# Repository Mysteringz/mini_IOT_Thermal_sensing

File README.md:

# CrowdAware

CrowdAware is a privacy-aware crowd monitoring prototype that uses low-resolution thermal sensors (MLX90640, 32x24) and edge processing on ESP32 nodes.

Instead of using RGB video, each node detects moving heat blobs, estimates person centroids, and transmits compact telemetry to a central receiver for live visualization and analytics.

## Why this project

Conventional crowd monitoring systems often trade privacy for visibility. CrowdAware is designed to keep personally identifying information out of the data path while still enabling:

- occupancy awareness
- movement and flow analysis
- congestion monitoring

## Current implementation status

This repository currently includes:

- ESP32 (Heltec WiFi LoRa 32 v3) node firmware for MLX90640 capture and on-device detection
- Wi-Fi UDP telemetry transport (current active path)
- Windows Python parser/visualizer for receiving and rendering node output
- hardware design files for a custom node PCB

The report references LoRaWAN architecture goals. In this codebase, Wi-Fi UDP is the active telemetry path used for development and visualization.

## Repository structure

```
Firmware/
	node/                          # ESP32 + MLX90640 node firmware
Visualization/
	parser_win.py                  # UDP receiver + OpenCV live visualizer
PCB Files/
	Altium Files/                  # Schematic + PCB source
	Gerber Files/                  # Manufacturing outputs
README.md
```

## System architecture

1. Sensor capture
- ESP32 reads thermal frames from MLX90640 (32x24) over I2C.

2. On-node processing
- Convert raw temperatures to 8-bit grayscale.
- Build/update a running background model.
- Detect moving hot regions with a lightweight pipeline.
- Extract person candidates (centroid and area).

3. Telemetry
- Serialize processing outputs and detections into a binary packet.
- Fragment into 4 UDP datagrams with sequence metadata.
- Transmit to the visualization host.

4. Central parsing and visualization
- Reassemble fragments.
- Decode intermediate images and detections.
- Render a 2x2 diagnostic view with overlays.

## Detection pipeline (firmware)

Implemented in the thermal processor:

1. Background subtraction
- Current frame minus running average background.

2. Morphological opening
- 3x3 erosion then 3x3 dilation to reduce noise and split weak bridges.

3. Gaussian blur
- 3x3 blur to smooth local artifacts.

4. Distance transform
- Approximate foreground distance map.

5. Watershed-like region extraction
- Connected-region labeling on thresholded distance map.
- Per-region centroid and area extraction.
- Area filtering via configurable min/max thresholds.

Adaptive behavior:

- Background is initialized over N frames.
- Background updates continue only when no people are detected to reduce contamination.

## Packet protocol

### Binary packet (reassembled payload)

- Header magic: `FE 01 FE 01`
- Payload length: uint16 little-endian
- Payload layout:
	- thermal image (768 bytes)
	- background image (768 bytes)
	- distance map (768 bytes)
	- labeled image (768 bytes)
	- num_detected (1 byte)
	- per detection: `y (1), x (1), area (uint16 LE)`

### UDP fragment packet

- Header magic: `FE 02 FE 02`
- Sequence: uint16 little-endian
- Fragment index: uint8
- Fragment count: uint8 (fixed at 4)
- Payload size: uint16 little-endian
- Payload bytes

Parser behavior:

- Waits for all 4 fragments for a `(sender_ip, sequence)` frame.
- Concatenates fragments in index order.
- Drops stale partial frames after timeout.

## Quick start

### 1) Firmware (Heltec WiFi LoRa 32 v3 node)

Prerequisites:

- Arduino IDE with Heltec WiFi LoRa 32(v3) board support
- MLX90640-compatible libraries required by the firmware

Open and configure:

- Sketch: `Firmware/node/node.ino`
- Main config: `Firmware/node/config.h`

Update at minimum:

- `WIFI_SSID`
- `WIFI_PASSWORD`
- `WIFI_REMOTE_IP_A..D` (host running parser)
- `WIFI_REMOTE_PORT` (default `5100`)
- `NODE_DEVICE_ID` (if using multiple nodes)

Upload firmware to ESP32, then open serial monitor (57600 baud) if needed for diagnostics.

### 2) Visualization receiver (Windows)

From repository root:

```powershell
pip install numpy opencv-python
python Visualization/parser_win.py
```

Expected behavior:

- Listener starts on `0.0.0.0:5100`.
- OpenCV window shows a 2x2 panel:
	- Raw image
	- Background
	- Distance map
	- Watershed labels
- Detected blobs and `(x,y)` coordinates are overlaid on the raw panel.

Press `q` to close the visualizer.

## Runtime tuning via serial commands

The firmware accepts newline-terminated commands over serial to tune processing without recompiling.

Supported command format:

```text
SET_DT_BG_THRESHOLD=<int>
SET_DT_MAX_DISTANCE=<int>
SET_MIN_PERSON_AREA=<int>
SET_MAX_PERSON_AREA=<int>
SET_BG_FRAME_COUNT=<int>
SET_TEMP_MIN=<float>
SET_TEMP_MAX=<float>
```

Notes:

- Changing `SET_BG_FRAME_COUNT` triggers background re-initialization.
- `TEMP_RANGE` is derived internally from min/max values.

## Hardware

Node hardware files are provided in:

- `PCB Files/Altium Files/`
- `PCB Files/Gerber Files/`

These include board-level design artifacts for the thermal node platform.

## Known limitations

- Current telemetry path in code is Wi-Fi UDP, not production LoRaWAN.
- Deployment and parameter management still rely on source-level/serial workflows.
- Multi-node global fusion and de-duplication are currently outside this repository's Python visualizer scope.

## Suggested next milestones

- Add a central server service for multi-node ingestion and global coordinate fusion.
- Build an operator/admin UI for node registration, calibration, and parameter control.
- Add replay logging and offline evaluation tools for algorithm benchmarking.

## Team

Innovation Wing IoT Team

- Ilo Japar
- Zhifang Li
- Nuth Kitchongcharoenying
- Netitorn Kawmali
- Pitimontreekul Chalida

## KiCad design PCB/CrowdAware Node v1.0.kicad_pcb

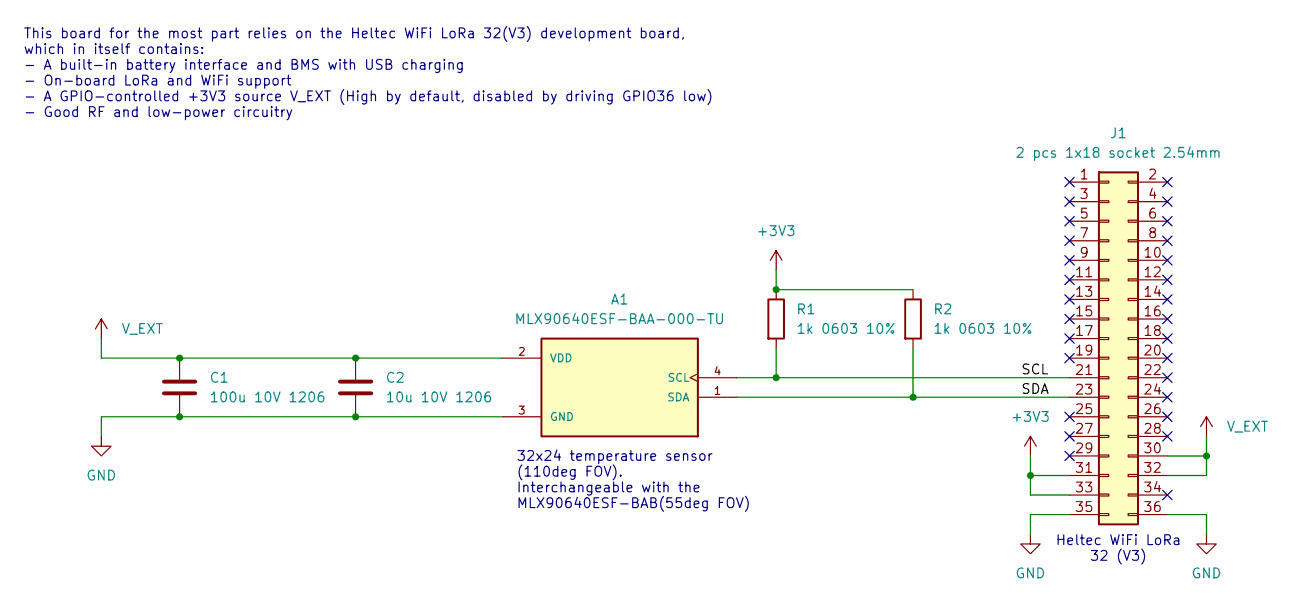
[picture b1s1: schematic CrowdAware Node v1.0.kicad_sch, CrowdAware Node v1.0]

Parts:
A1: MLX90640ESF-BAA-000-TU; PARTREV 11; Mouser No. 482-MLX90640ESFBAASP
C1: 100u 10V 1206; C_1206_3216Metric_Pad1.33x1.80mm_HandSolder; Mouser No. 81-GRM31CR61A107MA8L
C2: 10u 10V 1206; C_1206_3216Metric_Pad1.33x1.80mm_HandSolder; Mouser No. 81-GRM319R61A106KE9J
J1: 2 pcs 1x18 socket 2.54mm; Connector_HeltecWiFiLoRa32v3; Mouser No. 571-6-535541-6
R1, R2: 1k 0603 10%; R_0603_1608Metric_Pad0.98x0.95mm_HandSolder; Mouser No. 603-SR0603JR-7T1KL

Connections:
+3V3: J1.31, J1.33, R1.1, R2.1
/SCL: A1.4 (SCL), J1.21, R1.2
/SDA: A1.1 (SDA), J1.23, R2.2
GND: A1.3 (GND), C1.2, C2.2, J1.35, J1.36
V_EXT: A1.2 (VDD), C1.1, C2.1, J1.30, J1.32

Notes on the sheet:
This board for the most part relies on the Heltec WiFi LoRa 32(V3) development board, which in itself contains: - A built-in battery interface and BMS with USB charging - On-board LoRa and WiFi support - A GPIO-controlled +3V3 source V_EXT (High by default, disabled by driving GPIO36 low) - Good RF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
Heltec WiFi LoRa 32 (V3)
32x24 temperature sensor (110deg FOV). Interchangeable with the MLX90640ESF-BAB(55deg FOV)

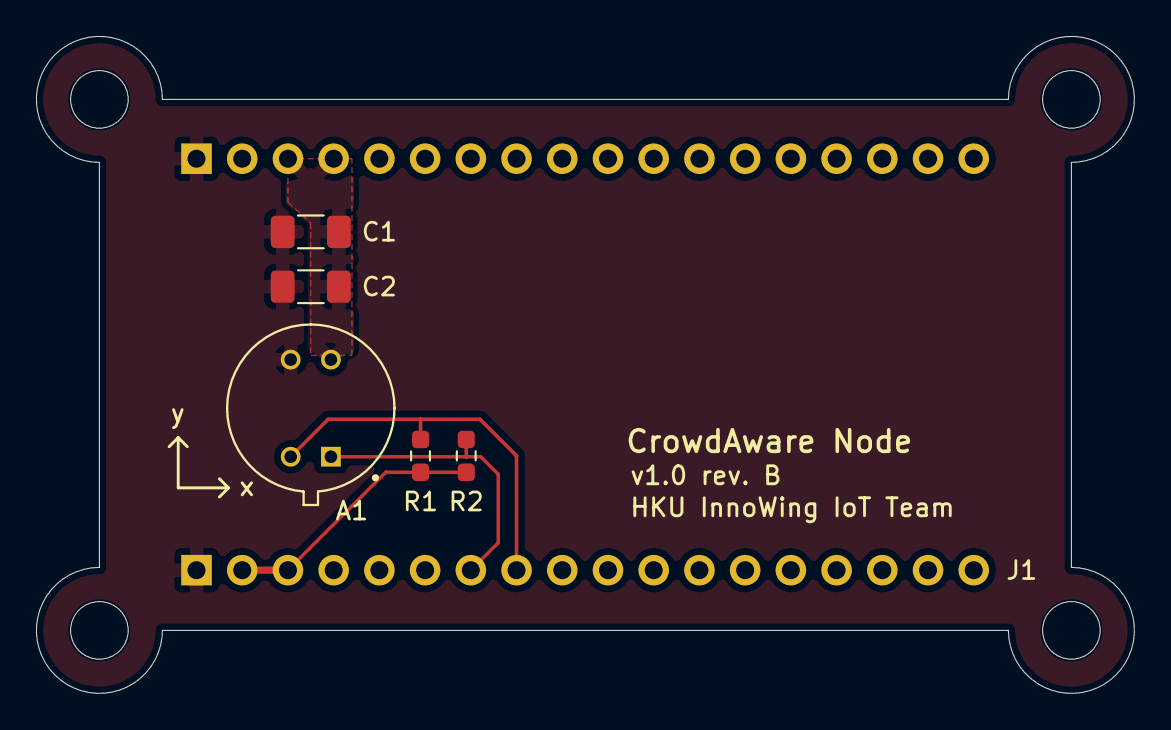
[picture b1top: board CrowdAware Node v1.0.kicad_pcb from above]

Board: 2 copper layers, 61.0 x 36.5 mm, 6 parts (1 on the bottom side), 5 nets.

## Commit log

2025-04-29 Rename plain_thermal_node.cpp to plain_thermal_node.ino
2025-06-03 Add visualization and cnn files and restructure repository
2025-06-11 Create PCB
2025-06-11 Create placeholder
2025-06-11 SCH Document
2025-06-11 Files for Altium (Schematics)
2025-06-19 Create Blank
2025-06-19 Create Spacer
2025-06-19 Version 1 of Thermal Camera PCB
2025-06-19 Delete Hardware/PCB directory
    Migrated over to home folder
2025-06-19 Delete PCB/Blank
    Cleanup
2025-06-19 Delete PCB/ThermalCamV1/Spacer
    Cleanup
2025-06-26 Added README file
2025-07-07 Delete PCB/ThermalCamV1 directory
    Updating to V1.2
2025-07-07 Spacer for PCB dir
2025-07-07 Updated to V1.1
2025-07-22 Uploaded PyTorch ONNX converter
2025-07-24 not working software, please fix
2025-07-24 Added feature testing for hardware and new lora+wifi code
2025-07-30 deleted broken files. Updated new version of normal thermal node with rgb based on people detection.
2025-08-01 Fixed num of LEDs. Change the indicator color to green.
2025-08-01 fix readme
2025-10-03 Update Readme with usage and requirements
    Added usage information about Arduino serial monitor and image processing requirements.
2025-10-03 Add STM32 code, model conversion pipeline, and ultralytics development
2025-10-03 Add TinyEngine Repository
2025-11-04 Add Mini TV Workshop Initial Code
2025-11-04 Move workshop folder location
2026-03-02 Removed Mini TV Repo from here; All relevant files already migrated to new Repo
2026-03-02 Added PCB Folder
2026-03-02 Moving files around in Hardware folder
2026-03-02 Reordered some functions
2026-03-04 Updated README.md due to deprecated Heltec board, structured into src files for Arduino, refactored out Web_interface
2026-03-04 Added incomplete README.md to thermal node 2.4, refactored camera_algorithm and web_interface
2026-03-05 Fixed type mismatch in OnDataSent; fixed type conflicts in refactored files
2026-03-05 Decided there was no point in putting everythin in subdirectories since Arduino is messy
2026-03-05 Fixed existing problems in Camera_algorithm, abstracted away struct_message into its own file (Data_packet), beginning refactoring for LED_Controller
2026-03-05 Fixed stray setup, now compiles properly
2026-03-06 Fixed led_set double declaration, factored out LoRaWAN server code to Web_interface, moved wifi, host, and ssid into user config
2026-03-06 Defined macros for LED Control
2026-03-11 Set correct lora params, fixed incorrect sequence flow, added serial print messages for more granular debugging
2026-03-30 Configured LoRa params as macros, added macros for led colours
2026-03-30 chore(repo): remove vendored YOLOv5 and third-party project
    Delete previously committed full source copies of YOLOv5 and another external OSS project.
    This cleans the repo and sets up a dependency-based install flow to be documented in the upcoming refactor README.
2026-03-30 Add thermal image processing and communication modules
    - Implemented serial communication for configurable parameters in `serial_comms.cpp` and `serial_comms.h`.
    - Developed thermal image processing algorithms in `thermal_image_processor.cpp` and `thermal_image_processor.h`, including background subtraction, morphological operations, and watershed segmentatio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
    - Created serialization functions for thermal data in `thermal_serializer.cpp` and `thermal_serializer.h`, enabling binary packet creation and fragmentation for transmission.
    - Established WiFi transport layer in `wifi_transport.cpp` and `wifi_transport.h` for sending serialized thermal data over UDP.
    - Introduced global configurable
2026-03-30 Reorganize project structure and add PCB files
    - Move node firmware files to Firmware/node directory
    - Reorganize PCB files to PCB Files directory with Gerber outputs
    - Clean up obsolete visualization scripts
    - Update .gitignore for new structure
2026-03-30 Update README.md to reflect project details and implementation status for CrowdAware
2026-03-30 Add image to README for better project visualization
    Added an image to the README to enhance visualization.
2026-03-30 Add GNU General Public License v3
2026-04-05 Migrated to KiCad. Simplified PCB
2026-04-06 Revised routing, changed pullup to 3v3
2026-04-06 Minor adjustment to trace spacing
2026-04-06 Removed ignorable file
2026-04-06 PCB file from previous revision
2026-04-08 Include BOM, Adjusted footprints to match
2026-04-08 Remove history folder
2026-04-08 Save project
2026-04-08 Add a simple LoRaWAN Uplink & Downlink connect between Heltec & WebUI
2026-04-14 Transfering data packages from Heltec into python variables.
2026-04-26 Migrated to pio
